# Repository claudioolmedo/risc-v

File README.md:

# risc-v-brain

Low cost electronic board to learn about RISC-V and use in educational projects for children. <br>
The objective is that the children have activities and after finishing the exercises they take them home to continue investigating. <br>
Created with Autodesk Eagle PCB. <br>
And Manufactured at https://jlcpcb.com/  <br>
# Steps to edit the file <br>
1. Download the Autodesk Eagle program: https://www.autodesk.com/products/eagle/free-download  <br>
Or you can download here with the version that the files were created in 2022:  <br>
  Linux: https://archive.org/details/autodesk-eagle-9.6.2-english-linux-64bit.tar  <br>
  Windows: https://archive.org/details/autodesk-eagle-9.6.2-english-win-64bit  <br>
  Mac: https://archive.org/details/autodesk-eagle-9.6.2-english-mac-64bit  <br>
  
2. Download Eagle Files RISC-V-Brain  <br>
3. Put the PCB and schematic files to the same folder.  <br>
4. Open the PCB file.  <br>

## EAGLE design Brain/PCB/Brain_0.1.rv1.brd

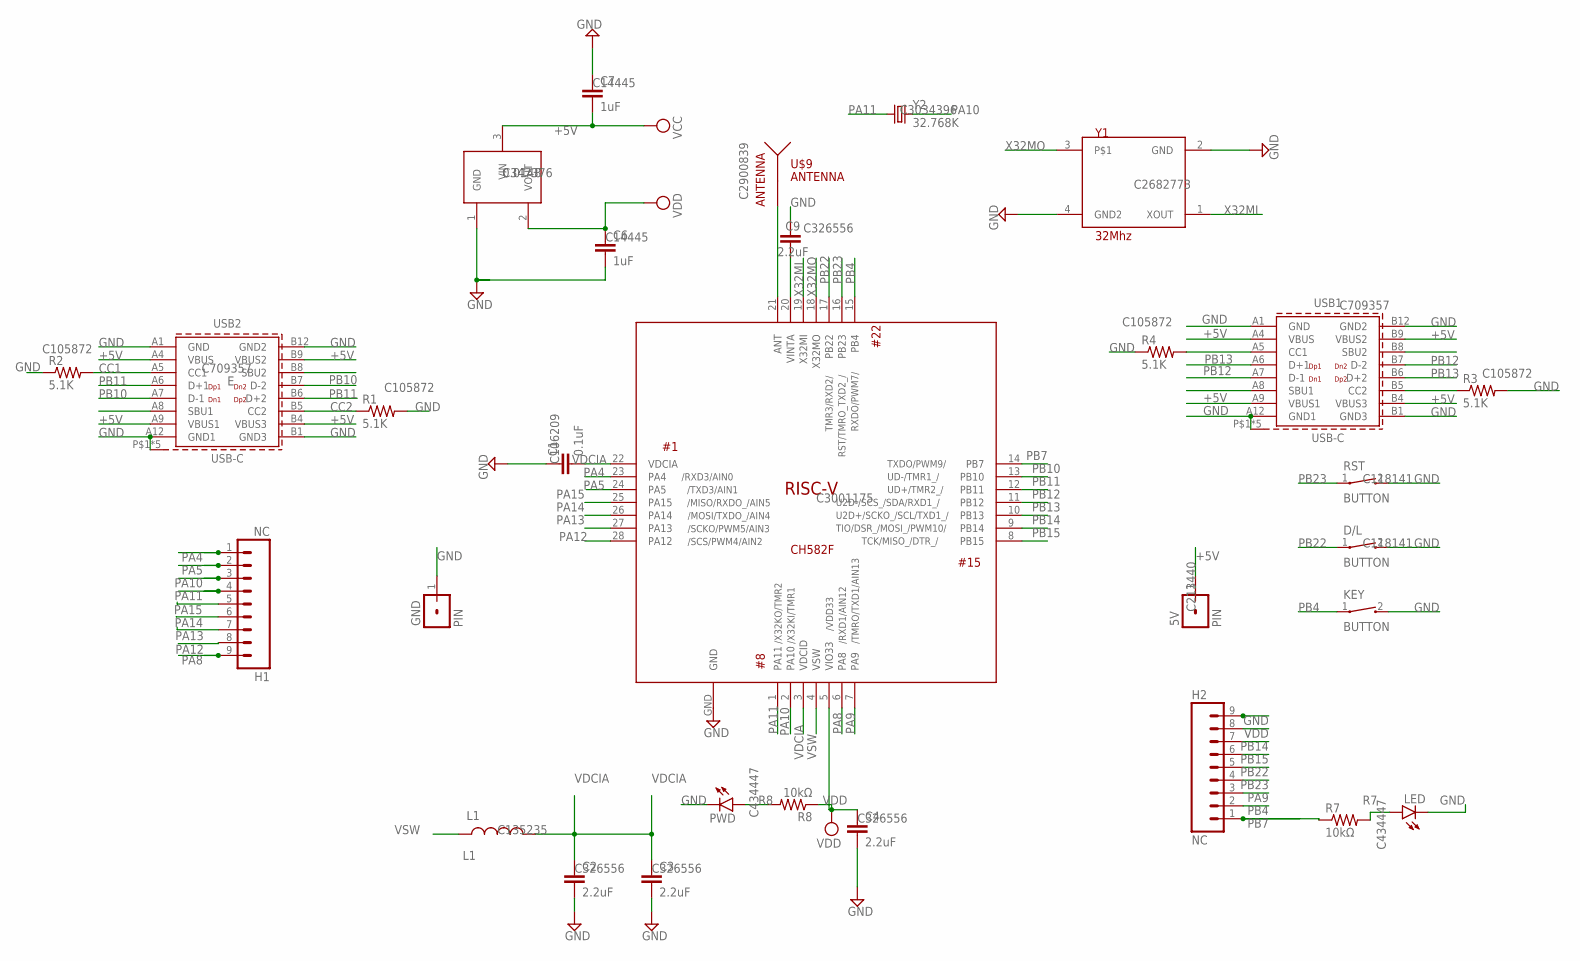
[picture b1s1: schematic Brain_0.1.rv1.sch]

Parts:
5V: PIN; 1X01; LCSC C213440
C1: 0.1uF; C1; LCSC C106209
C2, C3, C4, C9: 2.2uF; C1; LCSC C326556
C6, C7: 1uF; C1; LCSC C14445
D/L: BUTTON; SOD8037X250N; LCSC C118141
GND: PIN; 1X01; LCSC C213440
H1, H2: NC; 61300911821
KEY: BUTTON; SOD8037X250N; LCSC C118141
L1: L1; RESC3025X120N; LCSC C135235
LED: LED; CAPCP1005X40N; LCSC C434447
PWD: LED; CAPCP1005X40N; LCSC C434447
R1, R2, R3, R4: 5.1K; R0402; LCSC C105872
R7, R8: 10kΩ; R0402; LCSC C25744
RST: BUTTON; SOD8037X250N; LCSC C118141
U1: U1; SOT95P240X90-3N; LCSC C347376
U$8: RISC-V; QFN40P400X400X75-29T280N; LCSC C3001175
U$9: ANTENNA; CAPCP3015X50N; LCSC C2900839
USB1, USB2: 629722000214; LCSC C709357
Y1: Y1YSX211SL; OSCCC200X160X50N; LCSC C2682773
Y2: 32.768K; XTAL700X315X230N; LCSC C3034396

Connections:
+5V: 5V.1, C7.2, U1.3 (VIN), USB1.A4 (VBUS), USB1.A9 (VBUS1), USB1.B4 (VBUS3), USB1.B9 (VBUS2), USB2.A4 (VBUS), USB2.A9 (VBUS1), USB2.B4 (VBUS3), USB2.B9 (VBUS2)
CC1: R2.2, USB2.A5 (CC1)
CC2: R1.1, USB2.B5 (CC2)
GND: C1.1, C2.2, C3.2, C4.2, C6.2, C7.1, C9.1, D/L.2, GND.1, H2.9, KEY.2, LED.C, PWD.C, R1.2, R2.1, R3.2, R4.1, RST.2, U1.1 (GND), U$8.GND, USB1.A1 (GND), USB1.A12 (GND1), USB1.B1 (GND3), USB1.B12 (GND2), USB1.P$1 (SHIELD), USB1.S1 (SHIELD), USB1.S2 (SHIELD), USB1.S3 (SHIELD), USB1.S4 (SHIELD), USB2.A1 (GND), USB2.A12 (GND1), USB2.B1 (GND3), USB2.B12 (GND2), USB2.P$1 (SHIELD), USB2.S1 (SHIELD), USB2.S2 (SHIELD), USB2.S3 (SHIELD), USB2.S4 (SHIELD), Y1.2 (GND), Y1.4 (GND2)
unnamed: U$8.21 (ANT), U$9.1
unnamed: C9.2, U$8.20 (VINTA)
unnamed: R3.1, USB1.B5 (CC2)
unnamed: R4.2, USB1.A5 (CC1)
PA4: H1.1, U$8.23 (PA4)
PA5: H1.2, U$8.24 (PA5)
PA8: H1.9, U$8.6 (PA8)
PA9: H2.3, U$8.7 (PA9)
PA10: H1.3, U$8.2 (PA10), Y2.2
PA11: H1.4, U$8.1 (PA11), Y2.1
PA12: H1.8, U$8.28 (PA12)
PA13: H1.7, U$8.27 (PA13)
PA14: H1.6, U$8.26 (PA14)
PA15: H1.5, U$8.25 (PA15)
PB4: H2.2, KEY.1, U$8.15 (PB4)
PB7: H2.1, R7.1, U$8.14 (PB7)
PB10: U$8.13 (PB10), USB2.A7 (D-1), USB2.B7 (D-2)
PB11: U$8.12 (PB11), USB2.A6 (D+1), USB2.B6 (D+2)
PB12: U$8.11 (PB12), USB1.A7 (D-1), USB1.B7 (D-2)
PB13: U$8.10 (PB13), USB1.A6 (D+1), USB1.B6 (D+2)
PB14: H2.7, U$8.9 (PB14)
PB15: H2.6, U$8.8 (PB15)
PB22: D/L.1, H2.5, U$8.17 (PB22)
PB23: H2.4, RST.1, U$8.16 (PB23)
R7: LED.A, R7.2
R8: PWD.A, R8.2
VDCIA: C1.2, C2.1, C3.1, L1.2, U$8.3 (VDCID), U$8.22 (VDCIA)
VDD: C4.1, C6.1, H2.8, R8.1, U1.2 (VOUT), U$8.5 (VIO33)
VSW: L1.1, U$8.4 (VSW)
X32MI: U$8.19 (X32MI), Y1.1 (XOUT)
X32MO: U$8.18 (X32MO), Y1.3

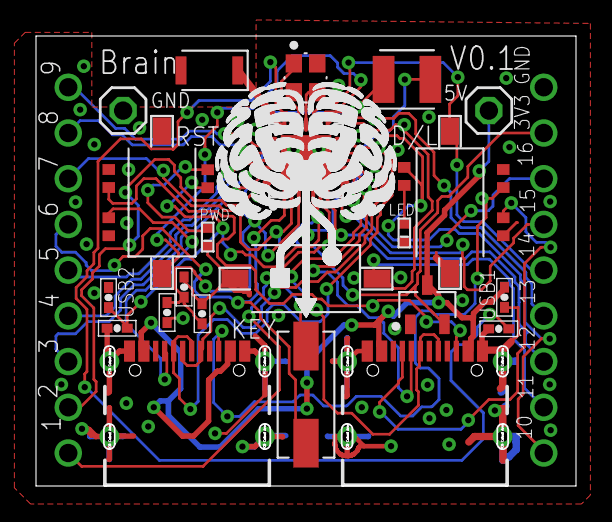
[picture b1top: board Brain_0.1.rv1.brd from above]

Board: 2 copper layers, 29.9 x 24.9 mm, 30 parts (0 on the bottom side), 35 nets.

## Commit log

2022-11-26 Documentation CH582F
    add documentation CH582F
2022-11-26 PCB RISC-V Brain
    First version of the Brain board, low cost RISC-V board to learn programming and Robotics
2022-11-26 organized folders
2022-11-26 BOOK RISC-V PT
2022-11-29 Books RISC-V CN ES KR
2022-12-09 Add documentation
2022-12-09 add gitignore
2022-12-09 Update Eagles Files add files for assembly
2022-12-09 Add files for production
